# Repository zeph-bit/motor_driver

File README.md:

# motor_driver

A simple motor driver circuit designed to interface with an STM32F072 DISCOVERY board and a Pololu 37D, item /#2824, brushed DC motor.

The driver includes a current sense feature to monitor the motor output and a temperature monitoring feature.

Below are photos of the assembled motor driver.

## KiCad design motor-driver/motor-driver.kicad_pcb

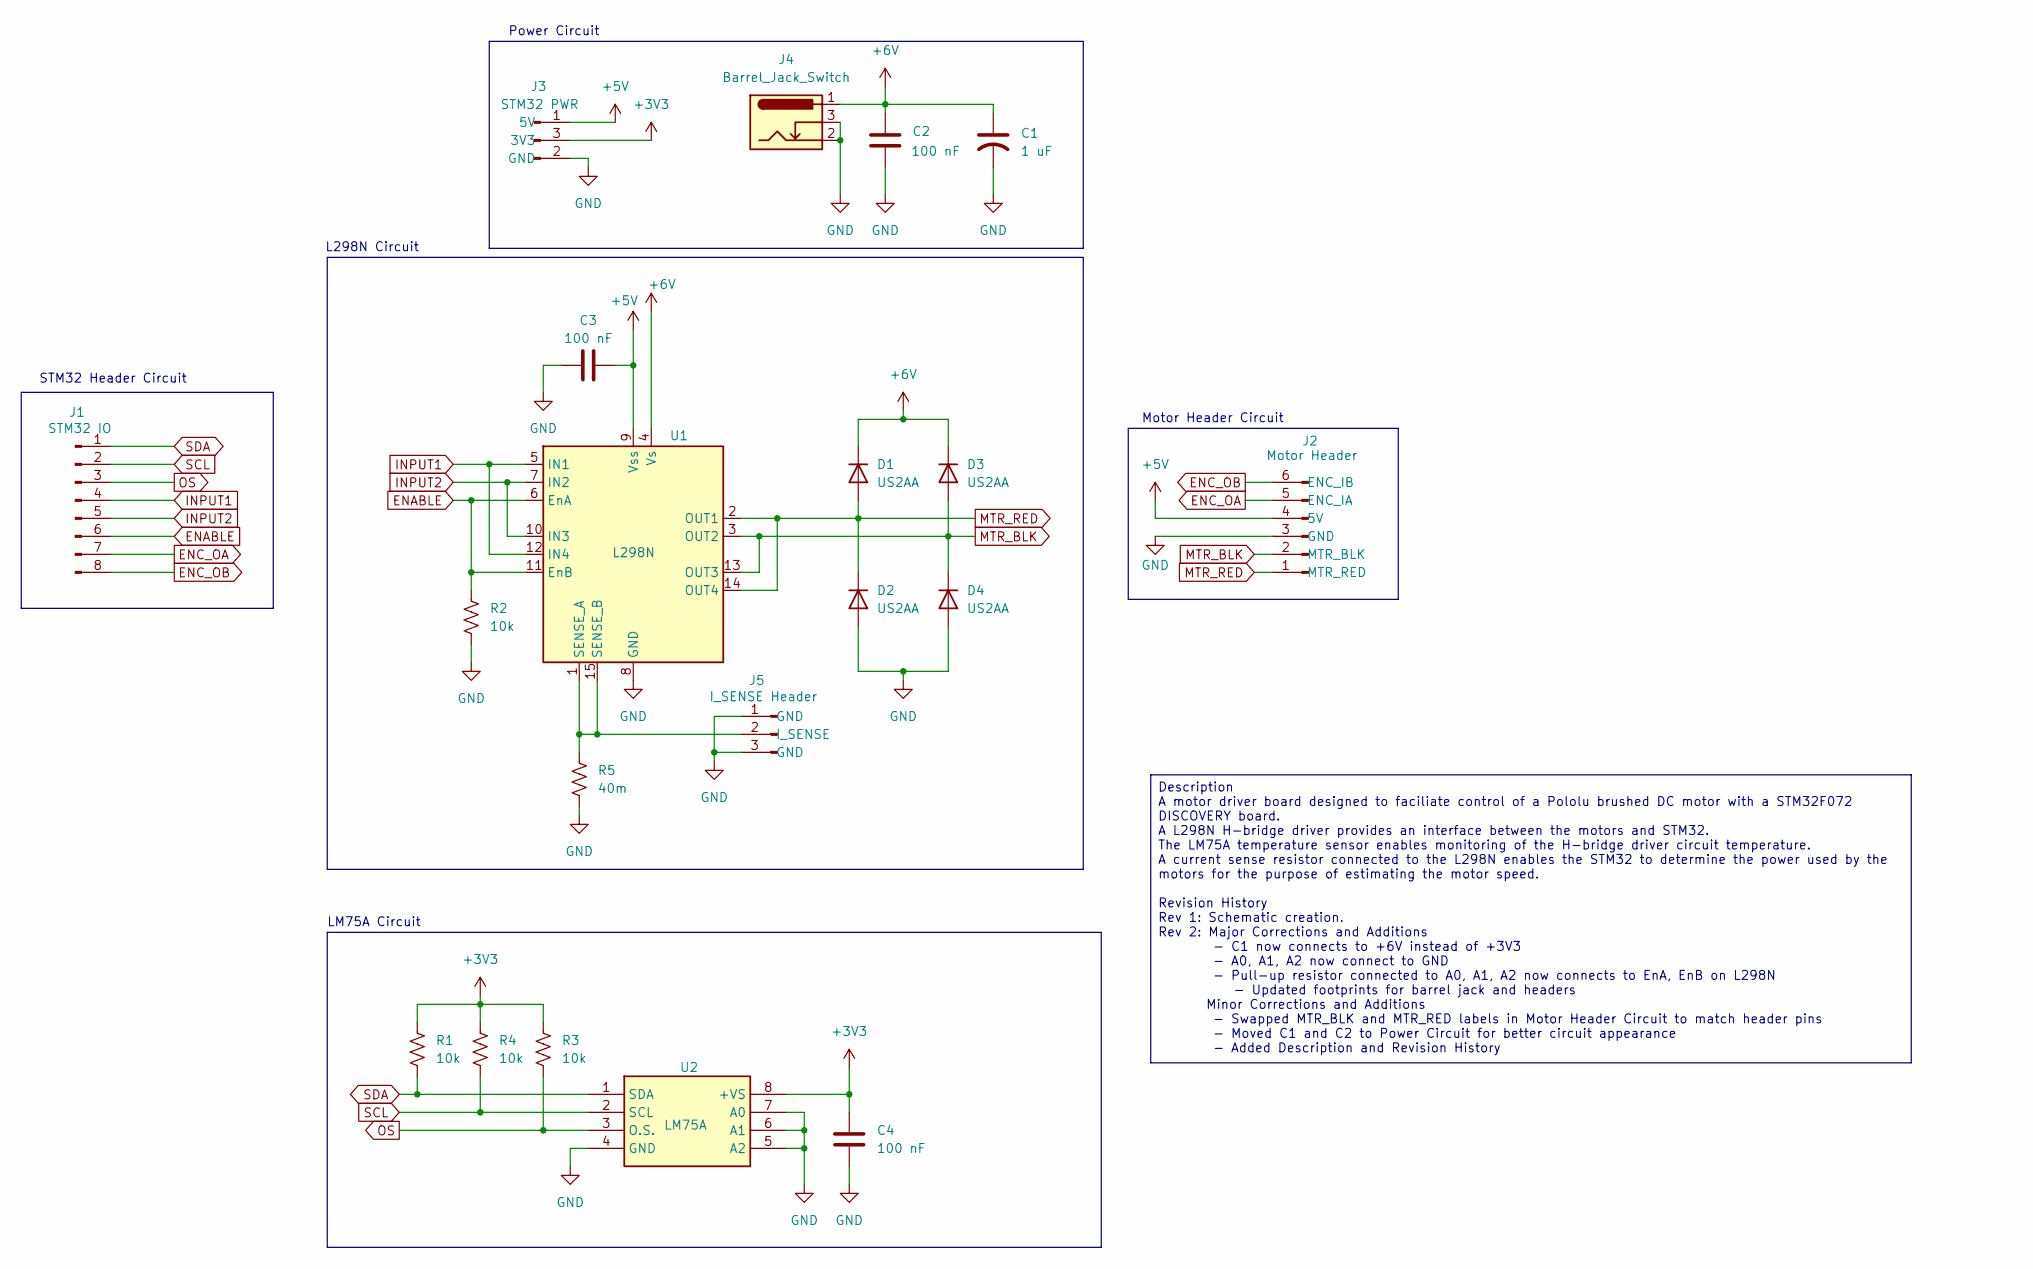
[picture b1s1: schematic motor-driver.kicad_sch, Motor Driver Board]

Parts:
C1: 1 uF; C_Radial_D5.0mm_H11.0mm_P2.00mm
C2, C3, C4: 100 nF; C_1206_3216Metric
D1, D2, D3, D4: US2AA; D_SMA
J1: STM32 IO; PinHeader_1x08_P2.54mm_Vertical
J2: Motor Header; PinHeader_1x06_P2.54mm_Vertical
J3: STM32 PWR; PinHeader_1x03_P2.54mm_Vertical
J4: Barrel_Jack_Switch; GRAVITECH_CON-SOCJ-2155
J5: I_SENSE Header; PinHeader_1x03_P2.54mm_Vertical
R1, R2, R3, R4: 10k; R_1206_3216Metric
R5: 40m; R_1206_3216Metric
U1: L298N; TO-220-15_P2.54x5.08mm_StaggerOdd_Lead4.58mm_Vertical
U2: LM75A; SOIC127P600X175-8N; Mouser Part Number 926-LM75AIMX/NOPB

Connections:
+3V3: C4.2, J3.3 (3V3), R1.1, R3.1, R4.1, U2.8 (+VS)
+5V: C3.2, J2.4 (5V), J3.1 (5V), U1.9 (Vss)
+6V: C1.1, C2.1, D1.1 (K), D3.1 (K), J4.1 (6V), U1.4 (Vs)
ENABLE: J1.6 (SCL), R2.1, U1.6 (EnA), U1.11 (EnB)
ENC_OA: J1.7 (ENC_OA), J2.5 (ENC_IA)
ENC_OB: J1.8 (ENC_OB), J2.6 (ENC_IB)
GND: C1.2, C2.2, C3.1, C4.1, D2.2 (A), D4.2 (A), J2.3 (GND), J3.2 (GND), J4.2, J4.3, J5.1 (GND), J5.3 (GND), R2.2, R5.2, U1.8 (GND), U2.4 (GND), U2.5 (A2), U2.6 (A1), U2.7 (A0)
INPUT1: J1.4 (OS), U1.5 (IN1), U1.12 (IN4)
INPUT2: J1.5 (SDA), U1.7 (IN2), U1.10 (IN3)
I_SENSE: J5.2 (I_SENSE), R5.1, U1.1 (SENSE_A), U1.15 (SENSE_B)
MTR_BLK: D3.2 (A), D4.1 (K), J2.2 (MTR_BLK), U1.3 (OUT2), U1.13 (OUT3)
MTR_RED: D1.2 (A), D2.1 (K), J2.1 (MTR_RED), U1.2 (OUT1), U1.14 (OUT4)
OS: J1.3 (ENABLE), R3.2, U2.3 (O.S.)
SCL: J1.2 (INPUT2), R4.2, U2.2 (SCL)
SDA: J1.1 (INPUT1), R1.2, U2.1 (SDA)

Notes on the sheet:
LM75A Circuit
L298N Circuit
Power Circuit
Motor Header Circuit
STM32 Header Circuit
Description A motor driver board designed to faciliate control of a Pololu brushed DC motor with a STM32F072 DISCOVERY board. A L298N H-bridge driver provides an interface between the motors and STM32. The LM75A temperature sensor enables monitoring of the H-bridge driver circuit temperature. A cur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

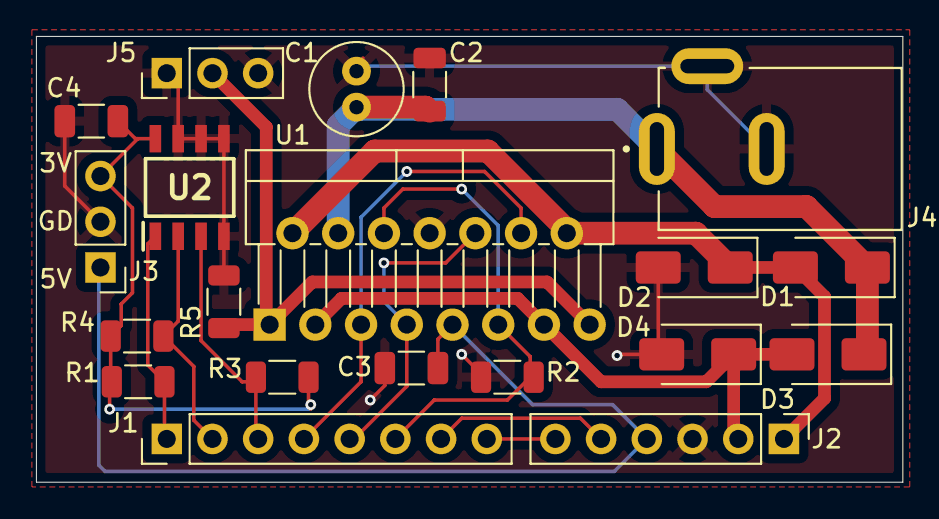
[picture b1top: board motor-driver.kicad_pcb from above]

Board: 2 copper layers, 48.1 x 24.8 mm, 20 parts (0 on the bottom side), 15 nets.

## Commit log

2026-05-11 Adding motor driver circuit schematic and PCB layout files.
2026-05-11 Create LICENSE
2026-05-11 Updated README and added pphoto of assembled driver.
2026-05-11 Added additional photo, renamed existing photo, updated README to include photos.
